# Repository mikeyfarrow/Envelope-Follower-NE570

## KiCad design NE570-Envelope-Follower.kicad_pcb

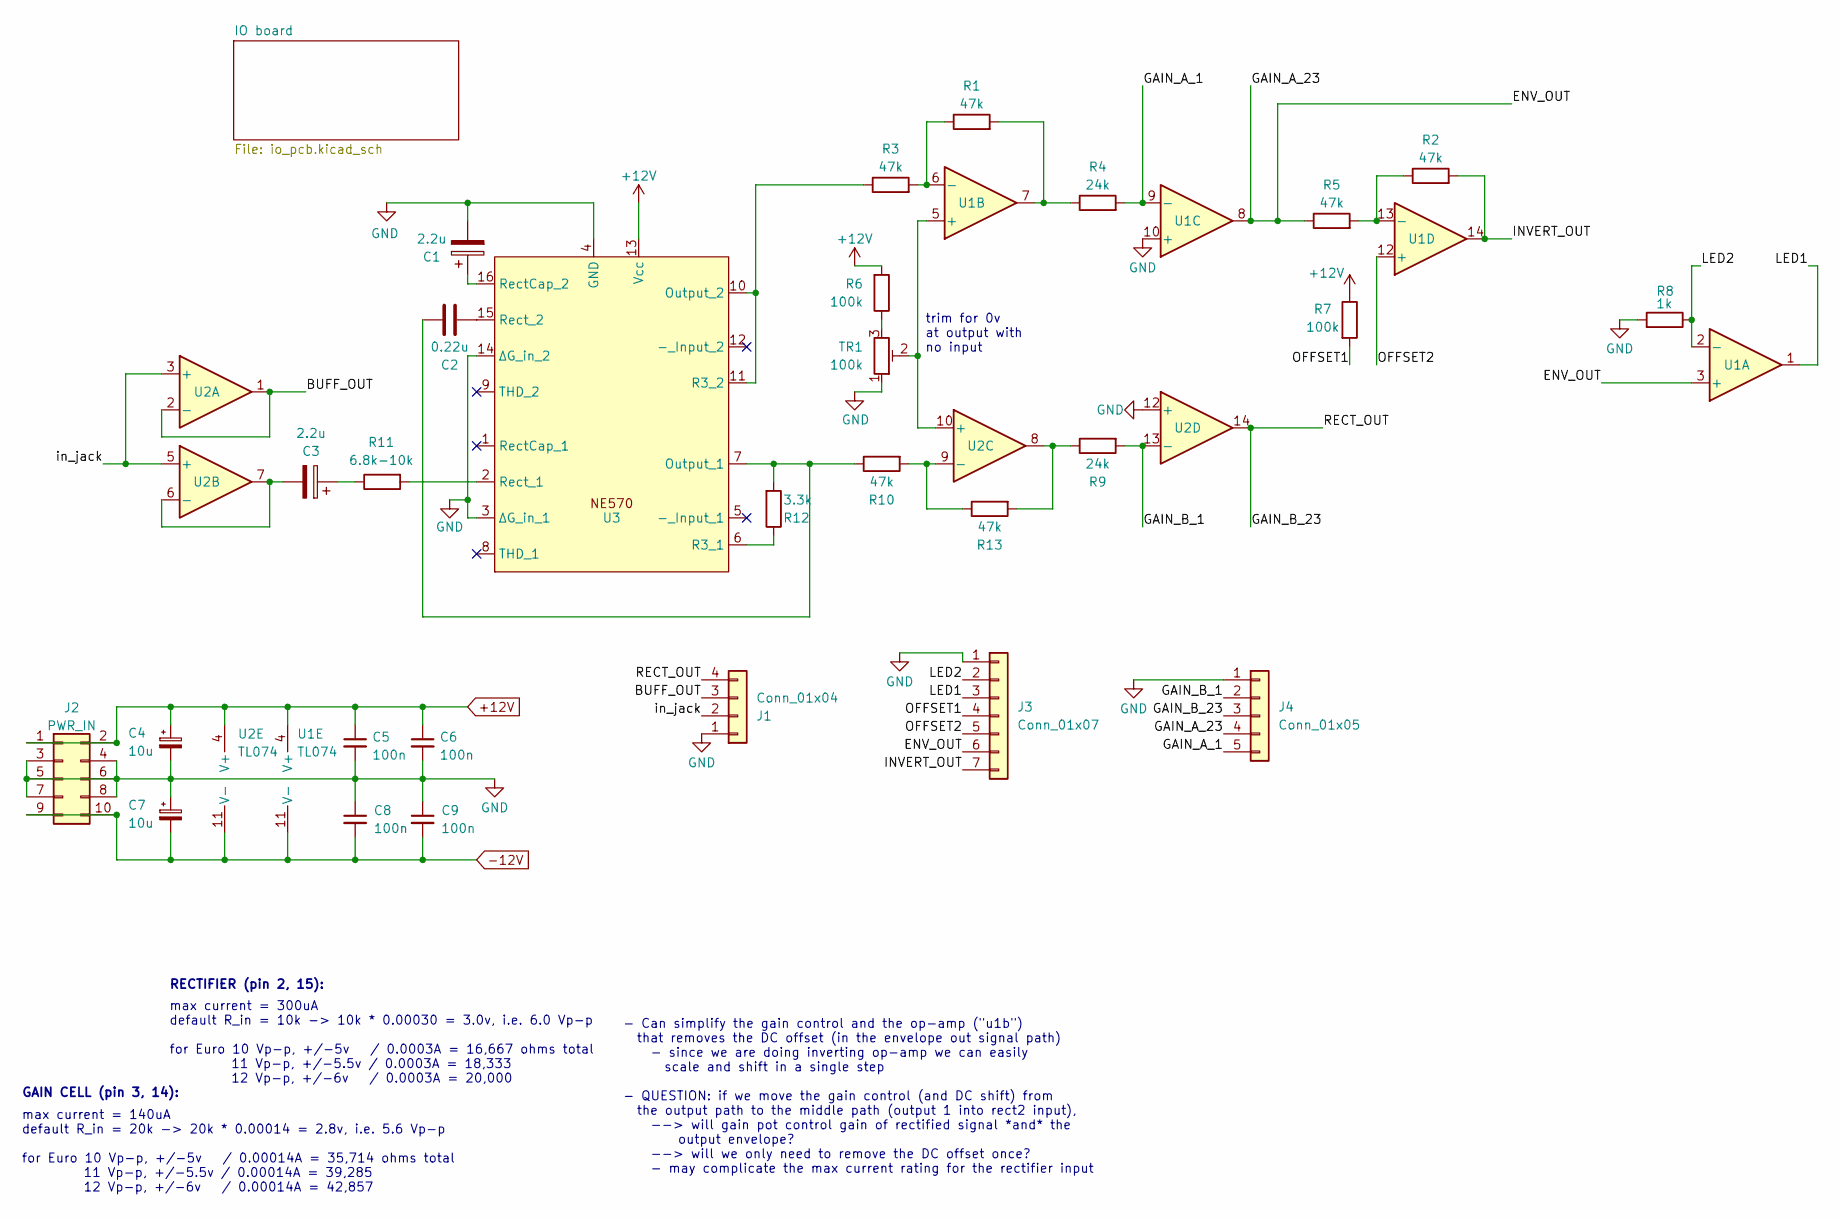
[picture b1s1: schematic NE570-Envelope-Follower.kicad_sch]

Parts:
C1, C3: 2.2u; FG18C0G1H101JNT06
C2: 0.22u; C_Disc_D3.0mm_W2.0mm_P2.50mm
C4, C7: 10u; CP_Elec_5x5.4; LCSC C263975
C5, C6, C8, C9: 100n; C_Disc_D3.0mm_W2.0mm_P2.50mm; LCSC C14663
J1: Conn_01x04; PinHeader_1x04_P2.54mm_Vertical
J2: PWR_IN; PinHeader_2x05_P2.54mm_Vertical
J3: Conn_01x07; PinHeader_1x07_P2.54mm_Vertical
J4: Conn_01x05; PinHeader_1x05_P2.54mm_Vertical
R1, R2, R3, R5, R13: 47k; R_Axial_DIN0204_L3.6mm_D1.6mm_P2.54mm_Vertical
R4: 24k; R_Axial_DIN0204_L3.6mm_D1.6mm_P2.54mm_Vertical
R6: 100k; R_Axial_DIN0204_L3.6mm_D1.6mm_P5.08mm_Horizontal
R7: 100k; R_Axial_DIN0204_L3.6mm_D1.6mm_P2.54mm_Vertical
R8: 1k; R_Axial_DIN0204_L3.6mm_D1.6mm_P2.54mm_Vertical
R9: 24k; R_Axial_DIN0204_L3.6mm_D1.6mm_P5.08mm_Horizontal
R10: 47k; R_Axial_DIN0204_L3.6mm_D1.6mm_P5.08mm_Horizontal
R11: 6.8k-10k; R_Axial_DIN0204_L3.6mm_D1.6mm_P2.54mm_Vertical
R12: 3.3k; R_Axial_DIN0204_L3.6mm_D1.6mm_P2.54mm_Vertical
TR1: 100k; Potentiometer_Bourns_3266W_Vertical
U1, U2: TL074; DIP-14_W7.62mm
U3: SOIC-16W_7.5x10.3mm_P1.27mm

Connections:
+12V: C4.1, C5.1, C6.1, J2.1, J2.2, R6.2, R7.1, U1.4 (V+), U2.4 (V+), U3.13 (Vcc)
-12V: C7.2, C8.2, C9.2, J2.9, J2.10, U1.11 (V-), U2.11 (V-)
/BUFF_OUT: J1.3, U2.1, U2.2 (-)
/ENV_OUT: J3.6, J4.4, R5.1, U1.3 (+), U1.8
/GAIN_A_1: J4.5, R4.2, U1.9 (-)
/GAIN_B_1: J4.2, R9.2, U2.13 (-)
/GAIN_B_23: J1.4, J4.3, U2.14
/INVERT_OUT: J3.7, R2.2, U1.14
/LED1: J3.3, U1.1
/LED2: J3.2, R8.1, U1.2 (-)
/OFFSET1: J3.4, R7.2
/OFFSET2: J3.5, U1.12 (+)
/in_jack: J1.2, U2.3 (+), U2.5 (+)
GND: C1.2, C4.2, C5.2, C6.2, C7.1, C8.1, C9.1, J1.1, J2.3, J2.4, J2.5, J2.6, J2.7, J2.8, J3.1, J4.1, R8.2, TR1.1, U1.10 (+), U2.12 (+), U3.3 (ΔG_in_1), U3.4 (GND), U3.14 (ΔG_in_2)
unnamed: C3.1, R11.1
unnamed: R1.2, R4.1, U1.7
unnamed: R6.1, TR1.3
unnamed: R9.1, R13.2, U2.8
unnamed: TR1.2, U1.5 (+), U2.10 (+)
unnamed: R1.1, R3.2, U1.6 (-)
unnamed: R2.1, R5.2, U1.13 (-)
unnamed: C3.2, U2.6 (-), U2.7
unnamed: R10.2, R13.1, U2.9 (-)
unnamed: C2.2, R10.1, R12.2, U3.7 (Output_1)
unnamed: R3.1, U3.10 (Output_2), U3.11 (R3_2)
unnamed: R12.1, U3.6 (R3_1)
unnamed: C1.1, U3.16 (RectCap_2)
unnamed: R11.2, U3.2 (Rect_1)
unnamed: C2.1, U3.15 (Rect_2)

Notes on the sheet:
max current = 300uA default R_in = 10k -> 10k * 0.00030 = 3.0v, i.e. 6.0 Vp-p for Euro 10 Vp-p, +/-5v / 0.0003A = 16,667 ohms total 11 Vp-p, +/-5.5v / 0.0003A = 18,333 12 Vp-p, +/-6v / 0.0003A = 20,000
- Can simplify the gain control and the op-amp ("u1b") that removes the DC offset (in the envelope out signal path) - since we are doing inverting op-amp we can easily scale and shift in a single step - QUESTION: if we move the gain control (and DC shift) from the output path to the middle path (ou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
RECTIFIER (pin 2, 15):
GAIN CELL (pin 3, 14):
trim for 0v at output with no input
max current = 140uA default R_in = 20k -> 20k * 0.00014 = 2.8v, i.e. 5.6 Vp-p for Euro 10 Vp-p, +/-5v / 0.00014A = 35,714 ohms total 11 Vp-p, +/-5.5v / 0.00014A = 39,285 12 Vp-p, +/-6v / 0.00014A = 42,857

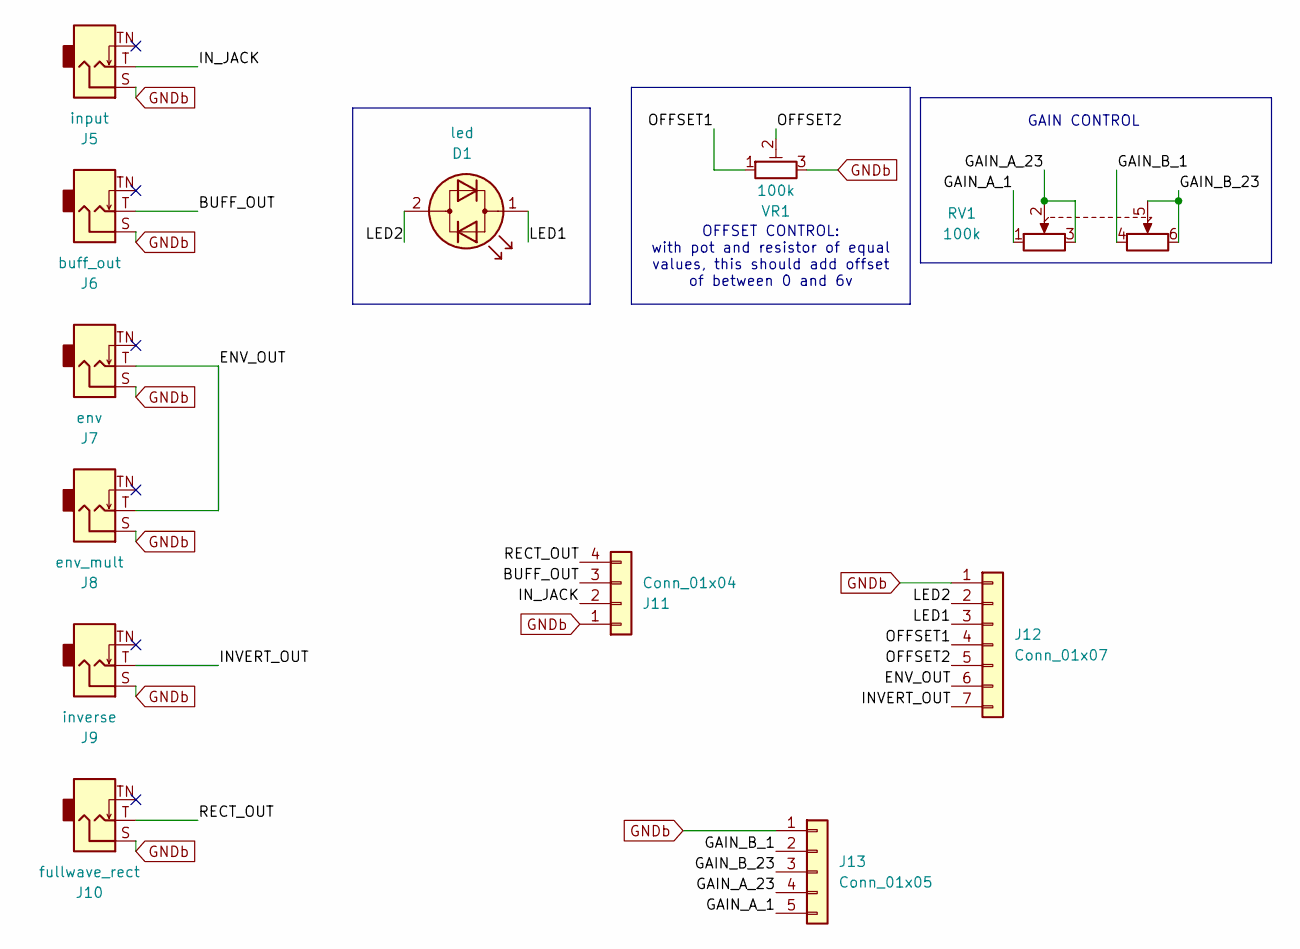
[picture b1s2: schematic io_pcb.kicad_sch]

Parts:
D1: led; LED_D3.0mm
J5: input; Thonkiconn
J6: buff_out; Thonkiconn
J7: env; Thonkiconn
J8: env_mult; Thonkiconn
J9: inverse; Thonkiconn
J10: fullwave_rect; Thonkiconn
J11: Conn_01x04; PinSocket_1x04_P2.54mm_Vertical
J12: Conn_01x07; PinSocket_1x07_P2.54mm_Vertical
J13: Conn_01x05; PinSocket_1x05_P2.54mm_Vertical
RV1: 100k; Potentiometer_Alpha_RD902F-40-00D_Dual_Vertical
VR1: 100k; Potentiometer_Alps_RK09K_Single_Vertical

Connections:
/IO board/BUFF_OUT: J6.T, J11.3
/IO board/ENV_OUT: J7.T, J8.T, J12.6
/IO board/GAIN_A_1: J13.5, RV1.1
/IO board/GAIN_A_23: J13.4, RV1.2, RV1.3
/IO board/GAIN_B_1: J13.2, RV1.4
/IO board/GAIN_B_23: J13.3, RV1.5, RV1.6
/IO board/INVERT_OUT: J9.T, J12.7
/IO board/IN_JACK: J5.T, J11.2
/IO board/LED1: D1.1 (KA), J12.3
/IO board/LED2: D1.2 (AK), J12.2
/IO board/OFFSET1: J12.4, VR1.1
/IO board/OFFSET2: J12.5, VR1.2
/IO board/RECT_OUT: J10.T, J11.4
GNDb: J5.S, J6.S, J7.S, J8.S, J9.S, J10.S, J11.1, J12.1, J13.1, VR1.3

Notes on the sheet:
GAIN CONTROL
OFFSET CONTROL: with pot and resistor of equal values, this should add offset of between 0 and 6v

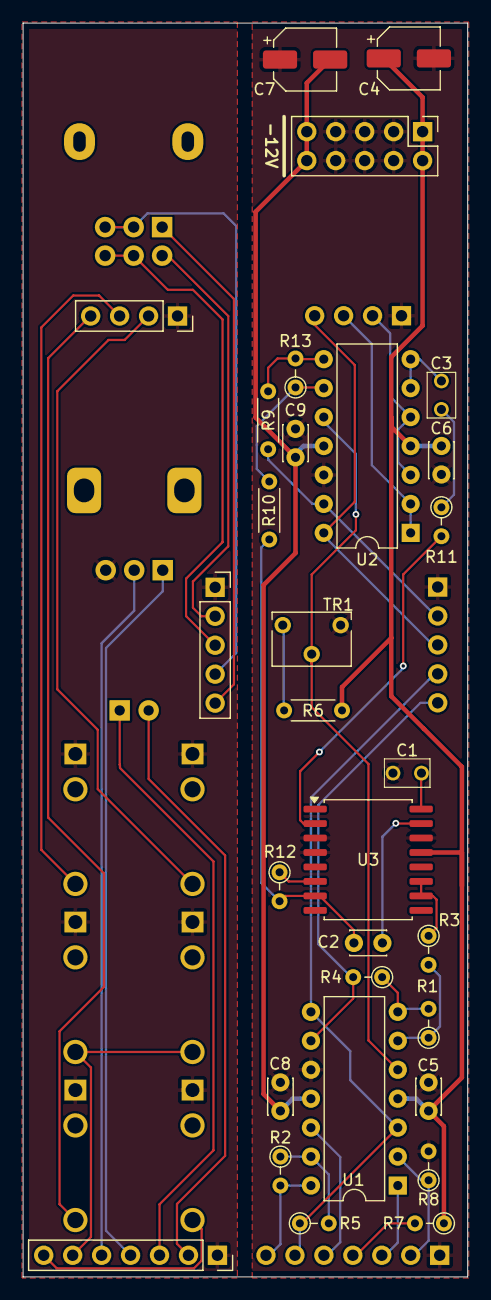
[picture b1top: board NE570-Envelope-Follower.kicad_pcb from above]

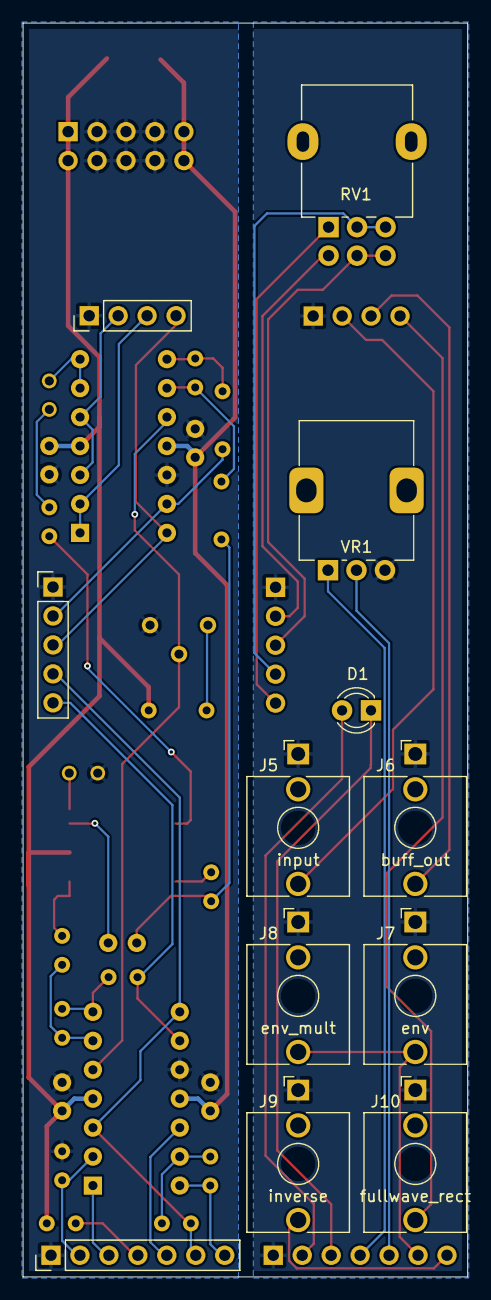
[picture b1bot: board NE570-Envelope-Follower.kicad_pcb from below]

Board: 2 copper layers, 39.0 x 110.0 mm, 42 parts (12 on the bottom side), 43 nets.

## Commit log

2024-08-20 initial
